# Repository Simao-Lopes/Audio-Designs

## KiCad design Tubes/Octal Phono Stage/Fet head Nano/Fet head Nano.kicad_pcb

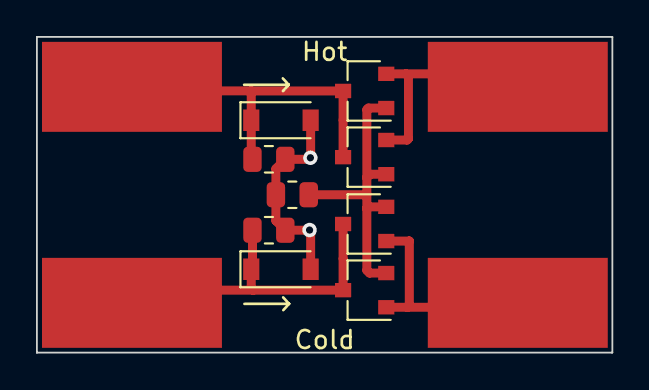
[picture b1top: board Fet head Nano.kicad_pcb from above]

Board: 2 copper layers, 32.0 x 17.5 mm, 12 parts (1 on the bottom side), 6 nets.

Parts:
22K, 22K#2: 22k; R_0805_2012Metric
56: 56; R_0805_2012Metric
Cold: SolderWirePad_1x01_SMD_5x10mm
D1, D2: 1N4148W; D_SOD-123
GND: SolderWirePad_1x01_SMD_5x10mm
Hot: SolderWirePad_1x01_SMD_5x10mm
Q1, Q2, Q3, Q4: Q_NJFET_SDG; SC-59

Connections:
GND: 22K.2, 22K#2.1, 56.1, D1.2 (A), D2.2 (A), GND.1
unnamed: 22K.1, D1.1 (K), Hot.1, Q1.3 (G), Q3.3 (G)
unnamed: 22K#2.2, Cold.1, D2.1 (K), Q2.3 (G), Q4.3 (G)
unnamed: Q1.2 (D), Q3.2 (D)
unnamed: Q2.1 (S), Q4.1 (S)
unnamed: 56.2, Q1.1 (S), Q2.2 (D), Q3.1 (S), Q4.2 (D)

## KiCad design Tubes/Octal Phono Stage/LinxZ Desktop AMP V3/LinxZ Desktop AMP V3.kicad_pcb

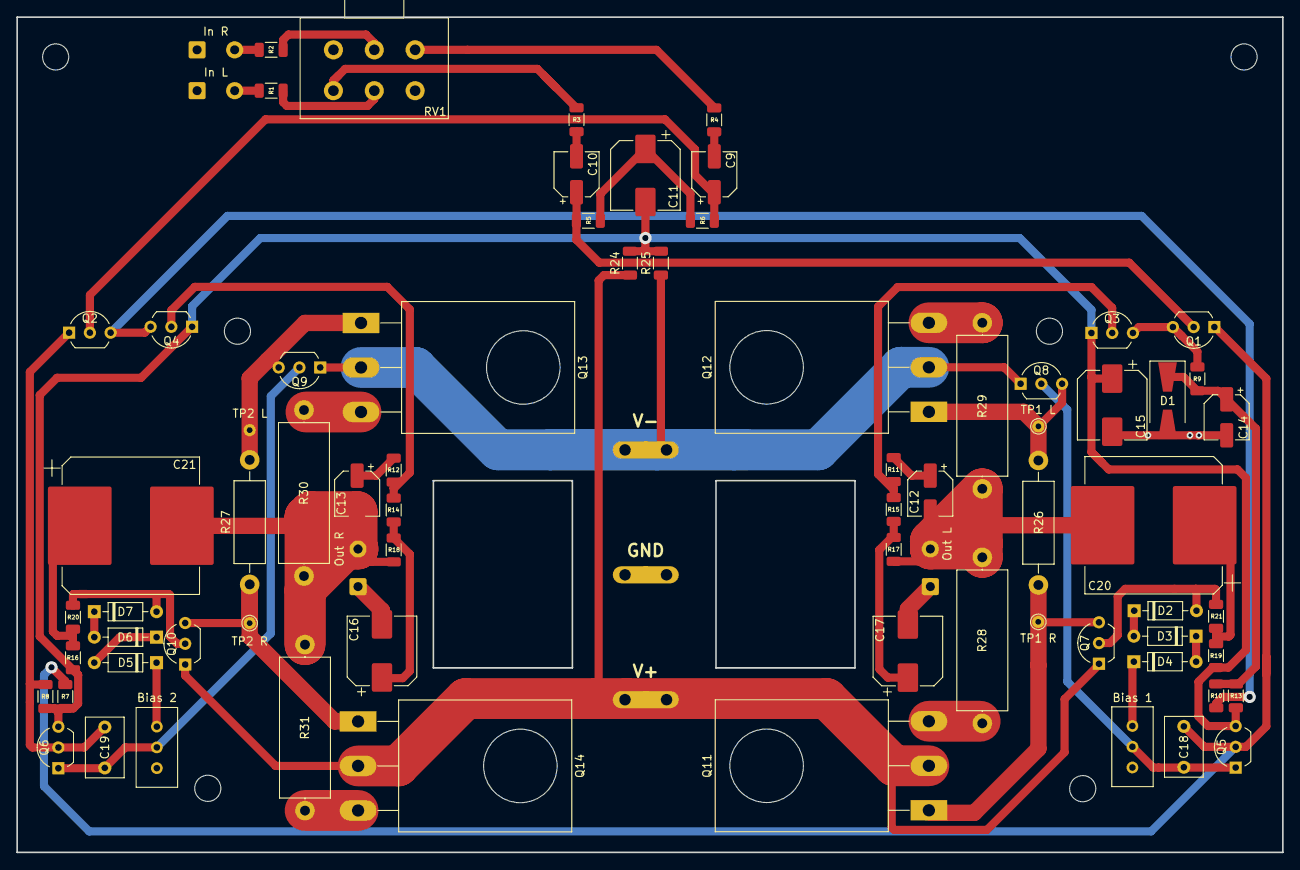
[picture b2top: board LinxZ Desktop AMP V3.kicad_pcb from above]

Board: 2 copper layers, 154.9 x 102.2 mm, 73 parts (0 on the bottom side), 48 nets.

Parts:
Bias 1, Bias 2: 1508; Potentiometer_Bourns_3296W_Vertical
C9, C10, C12, C13, C14: 10uF/35V; CP_Elec_5x5.3
C11, C15: 220uF/35V; CP_Elec_8x10
C16, C17: 100uF/35V; CP_Elec_8x10
C18, C19: 47pF; C_Rect_L7.2mm_W4.5mm_P5.00mm_FKS2_FKP2_MKS2_MKP2
C20, C21: 47uF/25v; CP_Elec_16x17.5
D1: 15V; D_SMA-SMB_Universal_Handsoldering
D2, D3, D4, D5, D6, D7: 1N4149; D_DO-35_SOD27_P7.62mm_Horizontal
In L: In L; SolderWire-0.5sqmm_1x02_P4.6mm_D0.9mm_OD2.1mm
In R: In R; SolderWire-0.5sqmm_1x02_P4.6mm_D0.9mm_OD2.1mm
Out L: Out L; SolderWire-0.5sqmm_1x02_P4.6mm_D0.9mm_OD2.1mm
Out R: Out R; SolderWire-0.5sqmm_1x02_P4.6mm_D0.9mm_OD2.1mm
Q1, Q2, Q3, Q4, Q8, Q9: BC556; TO-92_Inline_Wide
Q5, Q6, Q7, Q10: BC546; TO-92_Inline_Wide
Q11, Q14: TIP35; TO-247-3_Horizontal_TabDown
Q12, Q13: TIP42; TO-247-3_Horizontal_TabDown
R1, R2: 3.3K; R_1206_3216Metric
R3, R4: 1K; R_1206_3216Metric
R5, R6, R17, R18: 56K; R_1206_3216Metric
R7, R8, R13: 1.5K; R_1206_3216Metric
R9, R10: 15K; R_1206_3216Metric
R11, R12: 82K; R_1206_3216Metric
R14, R15: 5.6K; R_1206_3216Metric
R16, R19: 2.2K; R_1206_3216Metric
R20, R21: 2.7K; R_1206_3216Metric
R24, R25: 82 3W; R_1206_3216Metric
R26, R27: 470 3W; R_Axial_DIN0411_L9.9mm_D3.6mm_P15.24mm_Horizontal
R28, R29, R30, R31: 0.47 3W; R_Axial_DIN0617_L17.0mm_D6.0mm_P20.32mm_Horizontal
RV1: log 10K; Potentiometer_Alps_RK163_Dual_Horizontal
TP1 L, TP1 R, TP2 R: TestPoint_THTPad_D1.5mm_Drill0.7mm

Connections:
+24V: Q7.1 (C), Q10.1 (C), Q11.2 (C), Q14.2 (C), R24.1
-24V: Q8.1 (C), Q9.1 (C), Q12.2 (C), Q13.2 (C), R25.1
GND: C14.2, C15.2, C16.2, C17.2, D1.2 (A), In L.1, In R.1, Out L.1, Out R.1, RV1.3, RV1.4
In L: C10.2, R3.2
In R: C9.2, R4.2
unnamed: C9.1, Q2.2 (B), R6.2
unnamed: C10.1, Q1.2 (B), R5.1
unnamed: C11.1, R5.2, R6.1
unnamed: C11.2, C15.1, Q3.1 (C), Q4.1 (C), Q5.3 (E), Q6.3 (E), R7.2, R8.1, R13.2, R16.1, R19.2, R24.2, R25.2
unnamed: C12.1, R11.1
unnamed: C13.1, R12.2
unnamed: C14.1, D1.1 (K), R9.1, R10.2, R13.1
unnamed: C16.1, R14.2, R18.1
unnamed: C17.1, R15.2, R17.1
unnamed: C18.1, Q1.1 (C), Q5.2 (B), R7.1
unnamed: Bias 1.2, C18.2, Q5.1 (C), Q8.2 (B)
unnamed: C19.1, Q2.1 (C), Q6.2 (B), R8.2
unnamed: Bias 2.2, C19.2, Q6.1 (C), Q9.2 (B)
unnamed: C20.1, R19.1, R21.2
unnamed: C21.1, R16.2, R20.2
unnamed: D2.1 (K), D3.2 (A)
unnamed: D2.2 (A), Q7.2 (B), R21.1
unnamed: D3.1 (K), D4.2 (A)
unnamed: Bias 1.1, D4.1 (K)
unnamed: Bias 2.1, D5.1 (K)
unnamed: D5.2 (A), D6.1 (K)
unnamed: D6.2 (A), D7.1 (K)
unnamed: D7.2 (A), Q10.2 (B), R20.1
unnamed: In L.2, R1.1
unnamed: In R.2, R2.1
unnamed: Q1.3 (E), Q3.3 (E), R9.2
unnamed: Q2.3 (E), Q4.3 (E), R10.1
unnamed: Q3.2 (B), R11.2, R15.1
unnamed: Q4.2 (B), R12.1, R14.1
unnamed: Q10.3 (E), Q14.1 (B), R27.1, TP2 R.1
unnamed: Q7.3 (E), Q11.1 (B), R26.1, TP1 R.1
unnamed: Q11.3 (E), R28.1
unnamed: Q8.3 (E), Q12.1 (B), R26.2, TP1 L.1
unnamed: Q12.3 (E), R29.2
unnamed: Q9.3 (E), Q13.1 (B), R27.2
unnamed: Q13.3 (E), R30.2
unnamed: Q14.3 (E), R31.1
unnamed: R1.2, RV1.5
unnamed: R2.2, RV1.2
unnamed: R3.1, RV1.6
unnamed: R4.1, RV1.1
Out L: C12.2, C20.2, Out L.2, R17.2, R28.2, R29.1
Out R: C13.2, C21.2, Out R.2, R18.2, R30.1, R31.2

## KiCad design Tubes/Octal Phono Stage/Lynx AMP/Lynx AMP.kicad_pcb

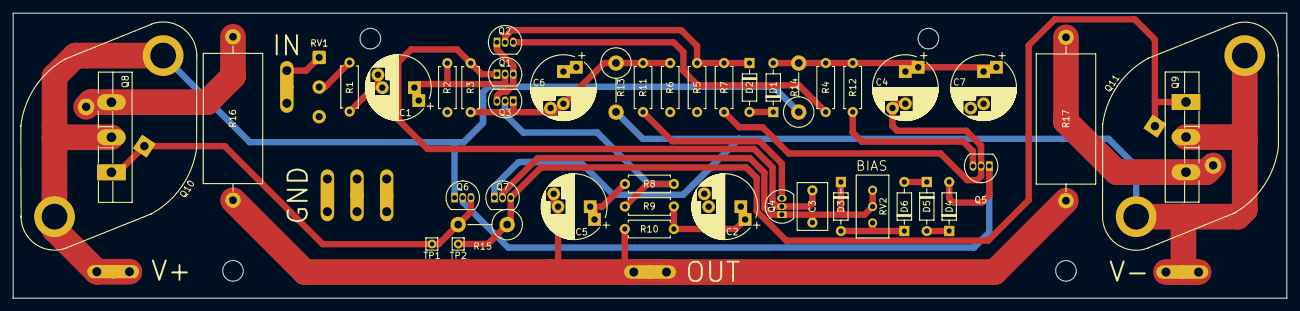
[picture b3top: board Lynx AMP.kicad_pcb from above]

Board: 2 copper layers, 198.0 x 44.3 mm, 56 parts (0 on the bottom side), 30 nets.

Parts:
 : MountingHole_3.2mm_M3
 #2,  #3,  #4: MountingHole_3.2mm_M3
C1: 10nF; CP_Radial_D10.0mm_P5.00mm_P7.50mm
C2: 10uF/25V; CP_Radial_D10.0mm_P5.00mm_P7.50mm
C3: 47pF; C_Rect_L7.2mm_W4.5mm_P5.00mm_FKS2_FKP2_MKS2_MKP2
C4: 47uF; CP_Radial_D10.0mm_P5.00mm_P7.50mm
C5: 10nF/16V; CP_Radial_D10.0mm_P5.00mm_P7.50mm
C6, C7: 220uF; CP_Radial_D10.0mm_P5.00mm_P7.50mm
D1, D2, D3, D4, D5, D6: 1N4149; D_DO-35_SOD27_P7.62mm_Horizontal
J1: IN; Spade Conector 6.3mm TE_1217861
J2: OUT; Spade Conector 6.3mm TE_1217861
J3: V+; Spade Conector 6.3mm TE_1217861
J4: V-; Spade Conector 6.3mm TE_1217861
J5, J6, J7: GND; Spade Conector 6.3mm TE_1217861
Q1, Q2, Q3, Q5, Q7: BC556; TO-92_Inline
Q4, Q6: BC546; TO-92_Inline
Q8: MJL21194; TO-264-3_Vertical
Q9: MJL21193; TO-264-3_Vertical
Q10: MJ15003; TO-3
Q11: MJ15004; TO-3
R1: 1K; R_Axial_DIN0207_L6.3mm_D2.5mm_P7.62mm_Horizontal
R2: 56K; R_Axial_DIN0207_L6.3mm_D2.5mm_P7.62mm_Horizontal
R3, R4, R5, R6, R7, R8, R9, R10, R11, R12: R_US; R_Axial_DIN0207_L6.3mm_D2.5mm_P7.62mm_Horizontal
R13, R14, R15: R_US; R_Axial_DIN0414_L11.9mm_D4.5mm_P7.62mm_Vertical
R16, R17: 0R33/5W; R_Axial_DIN0922_L20.0mm_D9.0mm_P25.40mm_Horizontal
RV1: 56K; SolderWire-0.5sqmm_1x03_P4.6mm_D0.9mm_OD2.1mm
RV2: 1K; Potentiometer_Bourns_3296W_Vertical
TP1, TP2: Pin_D0.7mm_L6.5mm_W1.8mm_FlatFork

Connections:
+VDC: J4.1, Q6.1 (C), Q8.2 (C), Q10.3 (C), R14.1
-VDC: J3.1, Q7.1 (C), Q9.2 (C), Q11.3 (C), R13.2
GND: C2.2, C6.1, C7.2, J5.1, J6.1, J7.1, R2.1, R5.1, R6.2, RV1.3
IN: J1.1, RV1.1
unnamed: C1.1, Q1.2 (B), R2.2
unnamed: C1.2, R1.2
unnamed: C2.1, R9.2, R10.1
unnamed: C3.1, Q1.1 (C), Q4.2 (B), R3.2
unnamed: C3.2, D3.1 (K), Q4.1 (C), Q7.2 (B), RV2.2, RV2.3
unnamed: C4.1, C7.1, D1.2 (A), R4.2, R12.2, R14.2
unnamed: C4.2, Q5.2 (B), R7.1
unnamed: C5.1, R8.2
unnamed: C6.2, Q3.1 (C), R3.1, R6.1, R11.1, R13.1
unnamed: D1.1 (K), D2.2 (A)
unnamed: D2.1 (K), Q2.2 (B), R5.2, R7.2
unnamed: D3.2 (A), D6.1 (K), RV2.1
unnamed: D4.1 (K), D5.2 (A)
unnamed: D4.2 (A), Q5.1 (C), Q6.2 (B)
unnamed: D5.1 (K), D6.2 (A)
unnamed: Q1.3 (E), Q2.1 (C), Q3.3 (E)
unnamed: Q2.3 (E), R4.1
unnamed: Q3.2 (B), R8.1, R9.1
unnamed: Q4.3 (E), R11.2
unnamed: Q5.3 (E), R12.1
unnamed: Q6.3 (E), Q8.1 (B), Q10.1 (B), R15.2, TP1.1
unnamed: Q8.3 (E), Q10.2 (E), R16.2
unnamed: Q7.3 (E), Q9.1 (B), Q11.1 (B), R15.1
unnamed: Q9.3 (E), Q11.2 (E), R17.1
unnamed: R1.1, RV1.2
OUT: C5.2, J2.1, R10.2, R16.1, R17.2

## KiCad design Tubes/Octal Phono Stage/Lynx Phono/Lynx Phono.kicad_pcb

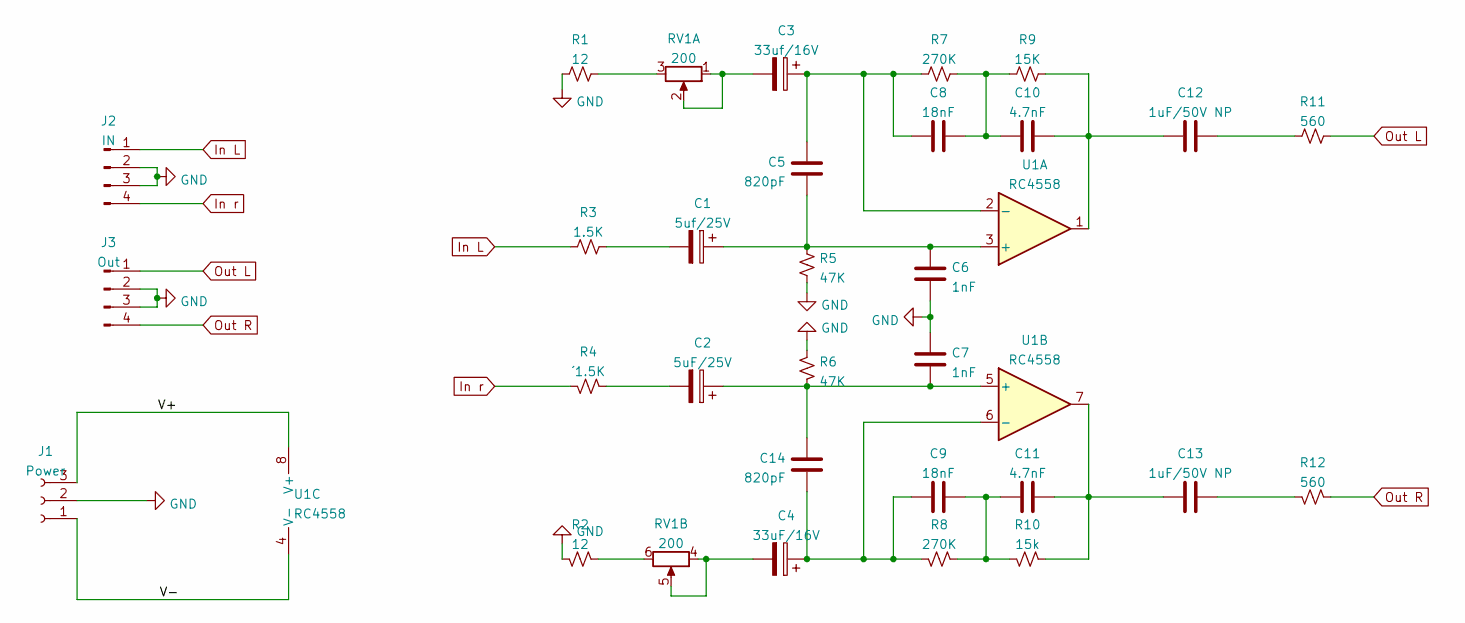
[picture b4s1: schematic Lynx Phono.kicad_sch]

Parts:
C1: 5uf/25V; CP_Radial_D10.0mm_P2.50mm_P5.00mm
C2: 5uF/25V; CP_Radial_D10.0mm_P2.50mm_P5.00mm
C3: 33uf/16V; CP_Radial_D10.0mm_P2.50mm_P5.00mm
C4: 33uF/16V; CP_Radial_D10.0mm_P2.50mm_P5.00mm
C5, C14: 820pF; C_Disc_D10.5mm_W5.0mm_P7.50mm
C6, C7: 1nF; C_Disc_D10.5mm_W5.0mm_P7.50mm
C8, C9: 18nF; C_Disc_D10.5mm_W5.0mm_P7.50mm
C10, C11: 4.7nF; C_Disc_D10.5mm_W5.0mm_P7.50mm
C12, C13: 1uF/50V NP; CP_Radial_D10.0mm_P2.50mm_P5.00mm
J1: Power; TerminalBlock_TE_282834-3_1x03_P2.54mm_Horizontal
J2: IN; TerminalBlock_TE_282834-4_1x04_P2.54mm_Horizontal
J3: Out; TerminalBlock_TE_282834-4_1x04_P2.54mm_Horizontal
R1, R2: 12; R_Axial_DIN0207_L6.3mm_D2.5mm_P7.62mm_Horizontal
R3: 1.5K; R_Axial_DIN0207_L6.3mm_D2.5mm_P7.62mm_Horizontal
R4: ´1.5K; R_Axial_DIN0207_L6.3mm_D2.5mm_P7.62mm_Horizontal
R5, R6: 47K; R_Axial_DIN0207_L6.3mm_D2.5mm_P7.62mm_Horizontal
R7, R8: 270K; R_Axial_DIN0207_L6.3mm_D2.5mm_P7.62mm_Horizontal
R9: 15K; R_Axial_DIN0207_L6.3mm_D2.5mm_P7.62mm_Horizontal
R10: 15k; R_Axial_DIN0207_L6.3mm_D2.5mm_P7.62mm_Horizontal
R11, R12: 560; R_Axial_DIN0207_L6.3mm_D2.5mm_P7.62mm_Horizontal
RV1: 200; Potentiometer_Alps_RK097_Dual_Horizontal
U1: RC4558; DIP-8_W7.62mm_Socket

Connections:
/V+: J1.3, U1.8 (V+)
/V-: J1.1, U1.4 (V-)
GND: C6.2, C7.1, J1.2, J2.2, J2.3, J3.2, J3.3, R1.2, R2.2, R5.1, R6.1; also elsewhere on the board
In L: J2.1, R3.1; also elsewhere on the board
In r: J2.4, R4.1; also elsewhere on the board
unnamed: C1.1, C5.2, C6.1, R5.2, U1.3 (+)
unnamed: C1.2, R3.2
unnamed: C2.2, R4.2
unnamed: C3.1, C5.1, C8.1, R7.2, U1.2 (-)
unnamed: C3.2, RV1.1, RV1.2
unnamed: C4.2, RV1.4, RV1.5
unnamed: C8.2, C10.1, R7.1, R9.2
unnamed: C10.2, C12.1, R9.1, U1.1
unnamed: C9.2, C11.1, R8.1, R10.2
unnamed: C11.2, C13.1, R10.1, U1.7
unnamed: C12.2, R11.2
unnamed: C13.2, R12.2
unnamed: C4.1, C9.1, C14.1, R8.2, U1.6 (-)
unnamed: C2.1, C7.2, C14.2, R6.2, U1.5 (+)
unnamed: R1.1, RV1.3
unnamed: R2.1, RV1.6
Out L: J3.1, R11.1; also elsewhere on the board
Out R: J3.4, R12.1; also elsewhere on the board

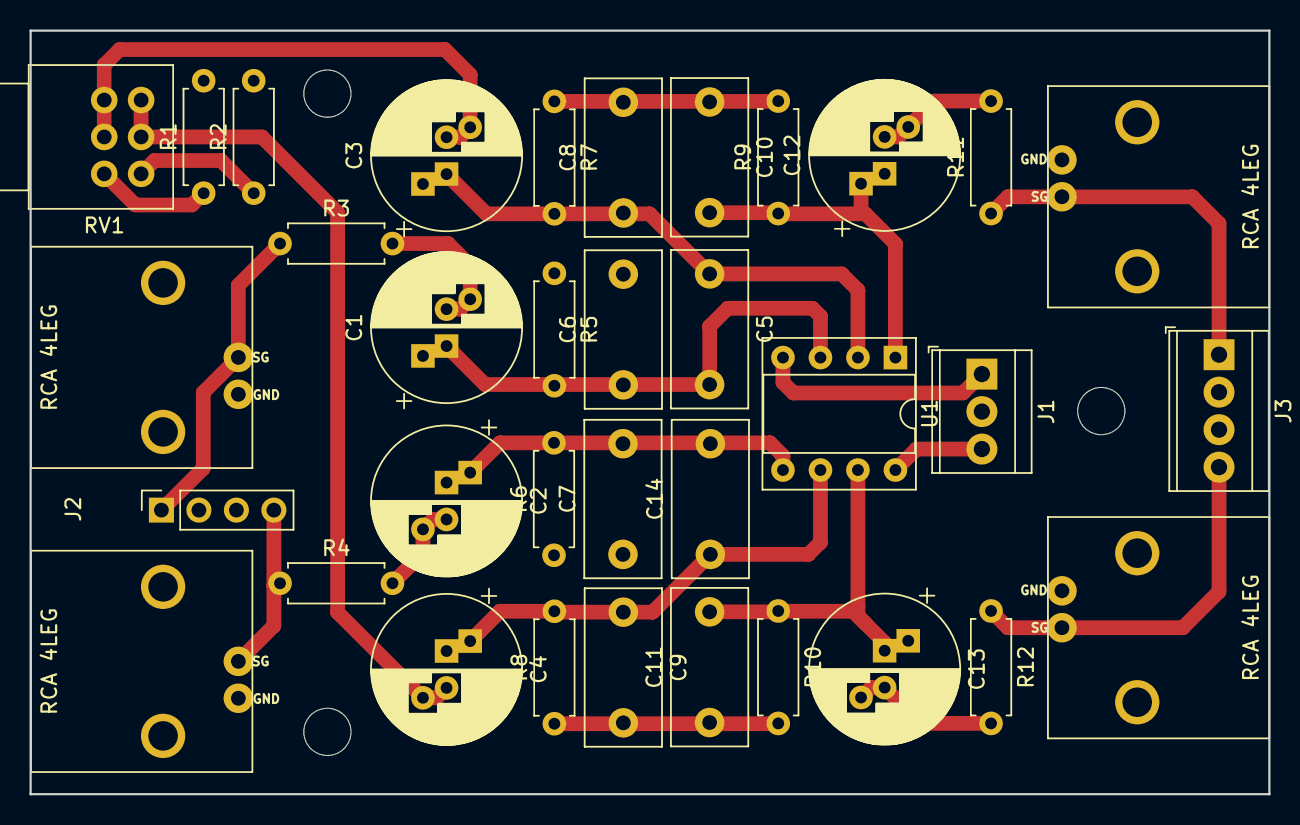
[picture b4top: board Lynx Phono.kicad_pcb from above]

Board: 2 copper layers, 83.9 x 51.7 mm, 35 parts (0 on the bottom side), 23 nets.

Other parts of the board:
RCA 4LEG, RCA 4LEG#2, RCA 4LEG#3, RCA 4LEG#4: RCA PHONO CONECTOR; RCA PANEL 2PIN FOOTPRINT

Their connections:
GND: RCA 4LEG.2, RCA 4LEG#2.2, RCA 4LEG#3.2, RCA 4LEG#4.2; also elsewhere on the board
In L: RCA 4LEG.1; also elsewhere on the board
In r: RCA 4LEG#4.1; also elsewhere on the board
Out L: RCA 4LEG#3.1; also elsewhere on the board
Out R: RCA 4LEG#2.1; also elsewhere on the board
